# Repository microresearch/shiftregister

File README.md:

# shiftregister
Software and hardware for the Shift Register project:

http://shiftregister.info/

NOW moved to: https://github.com/shiftregister/shiftregister

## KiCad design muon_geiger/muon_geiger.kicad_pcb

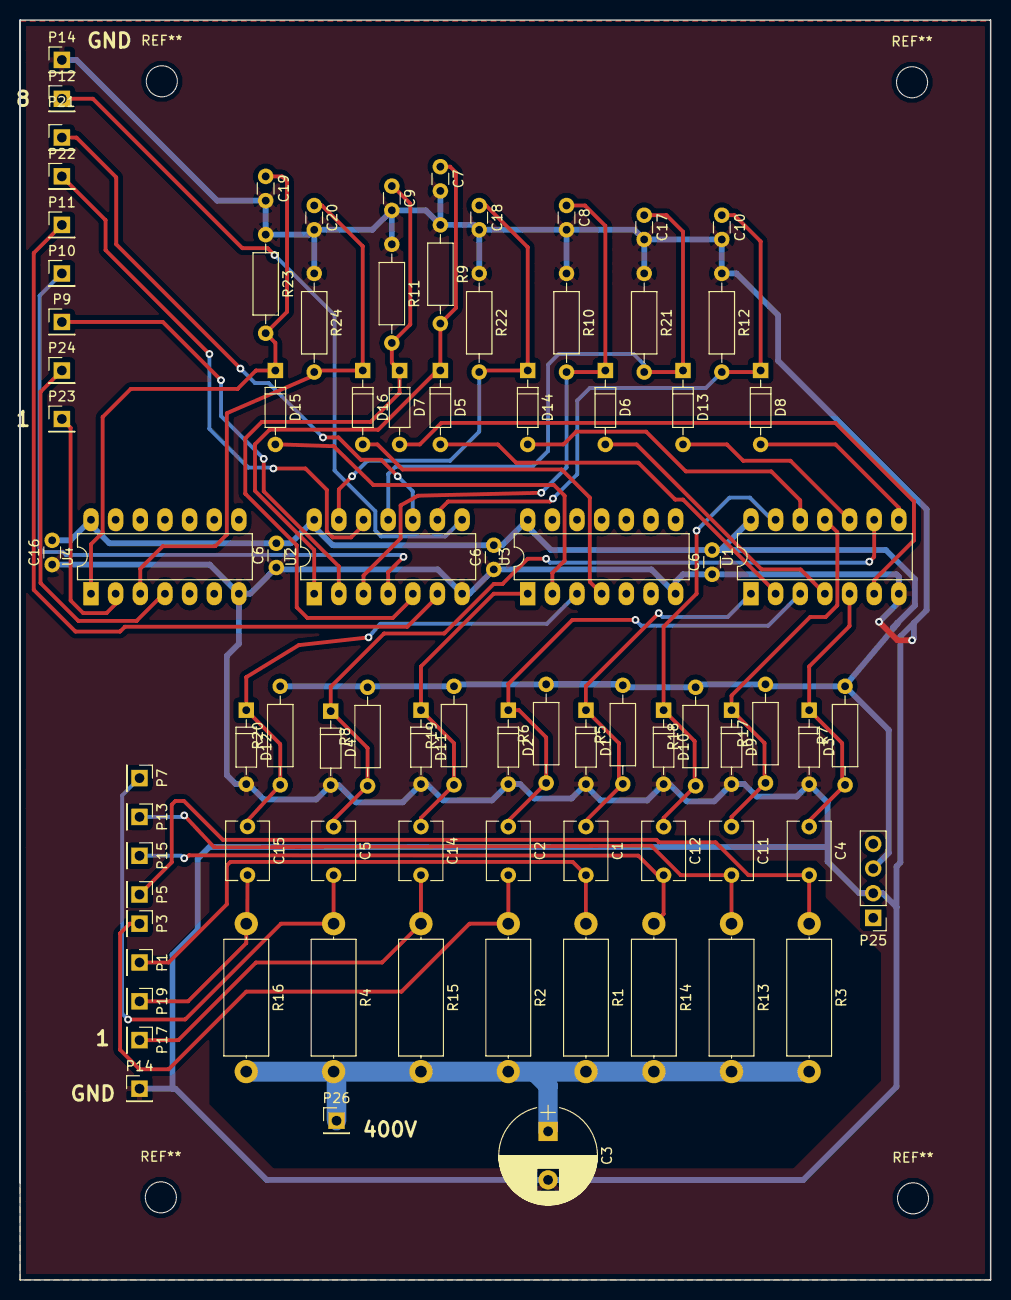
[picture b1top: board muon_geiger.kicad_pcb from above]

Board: 2 copper layers, 100.0 x 129.8 mm, 85 parts (0 on the bottom side), 43 nets.

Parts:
C1, C2, C4, C5, C11, C12, C14, C15: 10p; C_Disc_D6.0mm_W4.4mm_P5.00mm
C3: 1uF; CP_Radial_D10.0mm_P5.00mm
C6, C6#2, C6#3, C16: 100N; C_Disc_D3.0mm_W1.6mm_P2.50mm
C7, C8, C9, C10, C17, C18, C19, C20: 4n7; C_Disc_D3.0mm_W1.6mm_P2.50mm
D1, D2, D3, D4, D9, D10, D11, D12: 5V3; D_DO-35_SOD27_P7.62mm_Horizontal
D5, D6, D7, D8, D13, D14, D15, D16: 1N914; D_DO-35_SOD27_P7.62mm_Horizontal
P1, P3, P5, P7, P9, P10, P11, P12, P13, P14, P14#2, P15, P17, P19, P21, P22, P23, P24, P26: CONN_01X01; Pin_Header_Straight_1x01_Pitch2.54mm
P25: CONN_01X04; Pin_Header_Straight_1x04_Pitch2.54mm
R1, R2, R3, R4, R13, R14, R15, R16: 10M; R_Axial_DIN0414_L11.9mm_D4.5mm_P15.24mm_Horizontal
R5, R6, R7, R8, R17, R18, R19, R20: 100K; R_Axial_DIN0207_L6.3mm_D2.5mm_P10.16mm_Horizontal
R9, R10, R11, R12, R21, R22, R23, R24: 220K; R_Axial_DIN0207_L6.3mm_D2.5mm_P10.16mm_Horizontal
U1, U3: 74HC14; DIP-14_W7.62mm_LongPads
U2, U4: 74LS14; DIP-14_W7.62mm_LongPads

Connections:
+5V: C6.2, C6#2.2, C6#3.2, C16.2, P25.3, R5.2, R6.2, R7.2, R8.2, R17.2, R18.2, R19.2, R20.2, U1.14, U2.14, U3.14, U4.14
/400V: C3.1, P26.1, R1.2, R2.2, R3.2, R4.2, R13.2, R14.2, R15.2, R16.2
GND: C3.2, C6.1, C6#2.1, C6#3.1, C7.2, C8.2, C9.2, C10.2, C16.1, C17.2, C18.2, C19.2, C20.2, D1.2, D2.2, D3.2, D4.2, D9.2, D10.2, D11.2, D12.2, P14.1, P14#2.1, P25.2, R9.1, R10.1, R11.1, R12.1, R21.1, R22.1, R23.1, R24.1, U1.7, U2.7, U3.7, U4.7
unnamed: C1.1, D1.1, R5.1, U1.1
unnamed: C1.2, P1.1, R1.1
unnamed: C2.1, D2.1, R6.1, U1.3
unnamed: C2.2, P3.1, R2.1
unnamed: C4.1, D3.1, R7.1, U1.5
unnamed: C4.2, P5.1, R3.1
unnamed: C5.1, D4.1, R8.1, U1.9
unnamed: C5.2, P7.1, R4.1
unnamed: C7.1, D5.1, R9.2, U2.1
unnamed: C8.1, D6.1, R10.2, U2.3
unnamed: C9.1, D7.1, R11.2, U2.5
unnamed: C10.1, D8.1, R12.2, U2.9
unnamed: C11.1, D9.1, R17.1, U1.11
unnamed: C11.2, P13.1, R13.1
unnamed: C12.1, D10.1, R18.1, U1.13
unnamed: C12.2, P15.1, R14.1
unnamed: C14.1, D11.1, R19.1, U3.1
unnamed: C14.2, P17.1, R15.1
unnamed: C15.1, D12.1, R20.1, U3.3
unnamed: C15.2, P19.1, R16.1
unnamed: C17.1, D13.1, R21.2, U2.11
unnamed: C18.1, D14.1, R22.2, U2.13
unnamed: C19.1, D15.1, R23.2, U4.1
unnamed: C20.1, D16.1, R24.2, U4.3
unnamed: D5.2, U1.2
unnamed: D6.2, U1.4
unnamed: D7.2, U1.6
unnamed: D8.2, U1.8
unnamed: D13.2, U1.10
unnamed: D14.2, U1.12
unnamed: D15.2, U3.2
unnamed: D16.2, U3.4
unnamed: P9.1, U2.2
unnamed: P10.1, U2.4
unnamed: P11.1, U2.6
unnamed: P12.1, U2.8
unnamed: P21.1, U2.10
unnamed: P22.1, U2.12
unnamed: P23.1, U4.2
unnamed: P24.1, U4.4

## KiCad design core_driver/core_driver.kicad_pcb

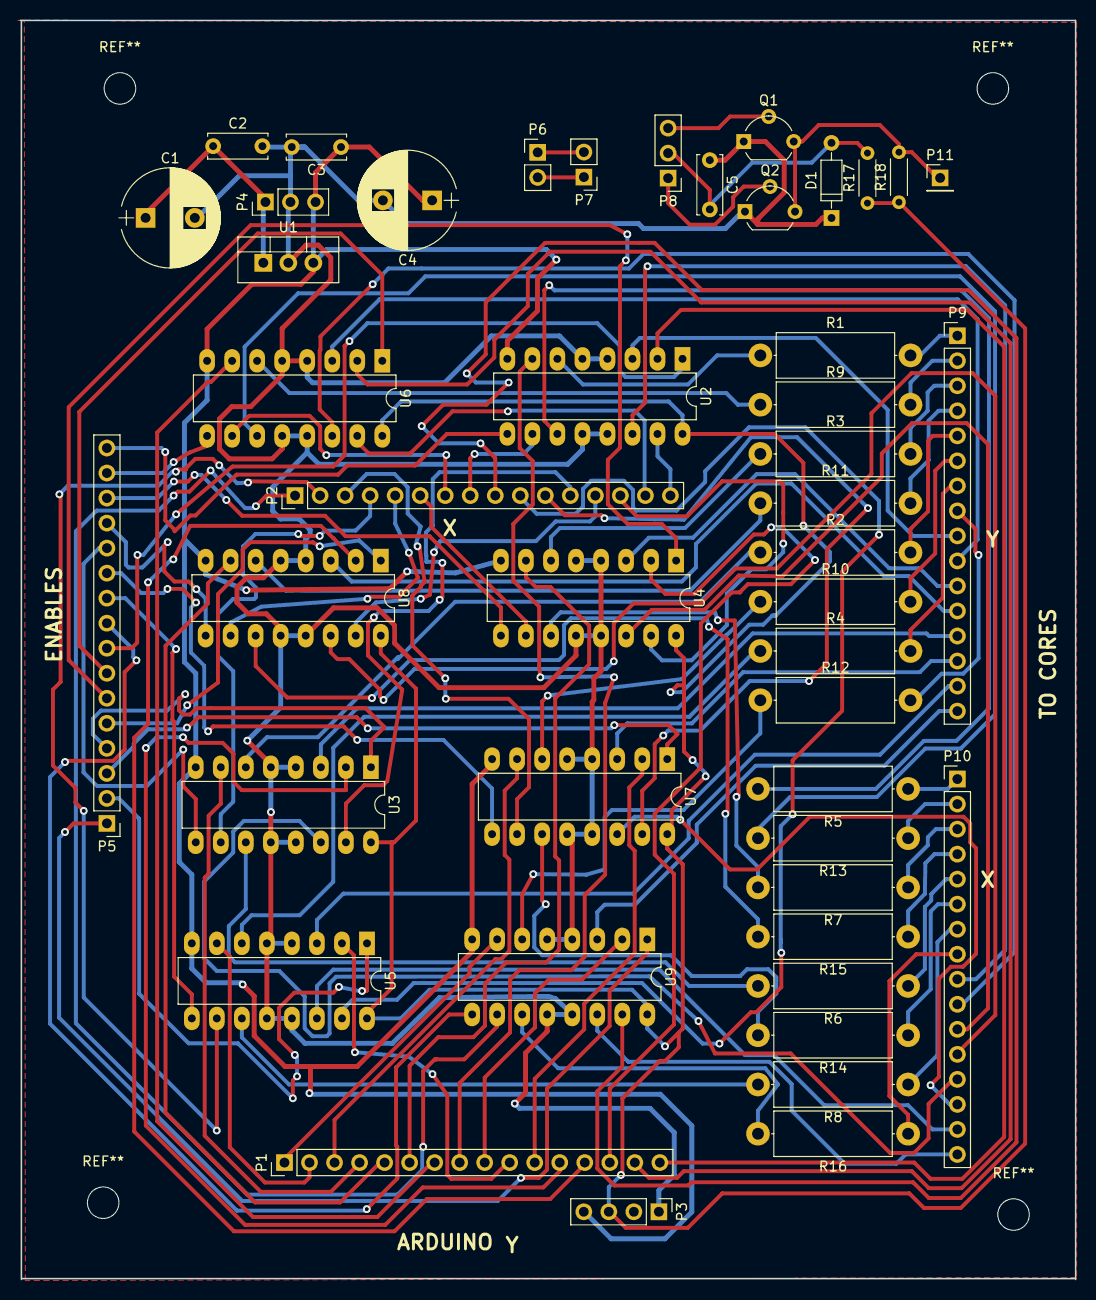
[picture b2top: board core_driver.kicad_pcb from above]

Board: 2 copper layers, 107.1 x 127.8 mm, 46 parts (0 on the bottom side), 106 nets.

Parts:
C1, C4: 10U; CP_Radial_D10.0mm_P5.00mm
C2, C3, C5: 100N; C_Disc_D6.0mm_W2.5mm_P5.00mm
D1: 1N4148; D_DO-35_SOD27_P7.62mm_Horizontal
P1, P2, P5, P9, P10: CONN_01X16; Pin_Header_Straight_1x16_Pitch2.54mm
P3: CONN_01X04; Pin_Header_Straight_1x04_Pitch2.54mm
P4, P8: CONN_01X03; Pin_Header_Straight_1x03_Pitch2.54mm
P6, P7: CONN_01X02; Pin_Header_Straight_1x02_Pitch2.54mm
P11: SENSE_DATA; Pin_Header_Straight_1x01_Pitch2.54mm
Q1, Q2: 2n3904; TO-92_Molded_Wide
R1, R2, R3, R4, R5, R6, R7, R8, R9, R10, R11, R12, R13, R14, R15, R16: 10R; R_Axial_DIN0414_L11.9mm_D4.5mm_P15.24mm_Horizontal
R17, R18: 10K; R_Axial_DIN0204_L3.6mm_D1.6mm_P5.08mm_Horizontal
U1: 7805; TO-220_Vertical
U2, U3, U4, U5, U6, U7, U8, U9: SN754410; DIP-16_W7.62mm_LongPads

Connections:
+5V: C3.1, C4.1, P3.4, P4.3, U1.3, U2.8, U3.8, U4.8, U5.8, U6.8, U7.8, U8.8, U9.8
/+9V: C1.1, C2.1, P4.1, U1.1
/EN_X0: P5.16, U2.9
/EN_X1: P5.15, U6.9
/EN_X2: P5.14, U4.9
/EN_X3: P5.13, U8.9
/EN_X4: P5.12, U3.9
/EN_X5: P5.11, U7.9
/EN_X6: P5.10, U5.9
/EN_X7: P5.9, U9.9
/EN_Y0: P5.8, U2.1
/EN_Y1: P5.7, U6.1
/EN_Y2: P5.6, U4.1
/EN_Y3: P5.5, U8.1
/EN_Y4: P5.4, U3.1
/EN_Y5: P5.3, U7.1
/EN_Y6: P5.2, U5.1
/EN_Y7: P5.1, U9.1
/HI_X0: P2.8, U2.10
/HI_X1: P2.7, U6.10
/HI_X2: P2.6, U4.10
/HI_X3: P2.5, U8.10
/HI_X4: P2.4, U3.10
/HI_X5: P2.3, U7.10
/HI_X6: P2.2, U5.10
/HI_X7: P2.1, U9.10
/HI_Y0: P1.8, U2.7
/HI_Y1: P1.7, U6.7
/HI_Y2: P1.6, U4.7
/HI_Y3: P1.5, U8.7
/HI_Y4: P1.4, U3.7
/HI_Y5: P1.3, U7.7
/HI_Y6: P1.2, U5.7
/HI_Y7: P1.1, U9.7
/IN_X0: P10.1, R5.1
/IN_X1: P10.2, R13.1
/IN_X2: P10.3, R7.1
/IN_X3: P10.4, R15.1
/IN_X4: P10.5, R6.1
/IN_X5: P10.6, R14.1
/IN_X6: P10.7, R8.1
/IN_X7: P10.8, R16.1
/IN_Y0: P9.1, R1.2
/IN_Y1: P9.2, R9.2
/IN_Y2: P9.3, R3.2
/IN_Y3: P9.4, R11.2
/IN_Y4: P9.5, R2.2
/IN_Y5: P9.6, R10.2
/IN_Y6: P9.7, R4.2
/IN_Y7: P9.8, R12.2
/LOGIC_PWR: P3.3, R17.1, R18.1, U2.16, U3.16, U4.16, U5.16, U6.16, U7.16, U8.16, U9.16
/LOW_X0: P2.16, U2.15
/LOW_X1: P2.15, U6.15
/LOW_X2: P2.14, U4.15
/LOW_X3: P2.13, U8.15
/LOW_X4: P2.12, U3.15
/LOW_X5: P2.11, U7.15
/LOW_X6: P2.10, U5.15
/LOW_X7: P2.9, U9.15
/LOW_Y0: P1.16, U2.2
/LOW_Y1: P1.15, U6.2
/LOW_Y2: P1.14, U4.2
/LOW_Y3: P1.13, U8.2
/LOW_Y4: P1.12, U3.2
/LOW_Y5: P1.11, U7.2
/LOW_Y6: P1.10, U5.2
/LOW_Y7: P1.9, U9.2
/OUT_X0: P10.9, U2.14
/OUT_X1: P10.10, U6.14
/OUT_X2: P10.11, U4.14
/OUT_X3: P10.12, U8.14
/OUT_X4: P10.13, U3.14
/OUT_X5: P10.14, U7.14
/OUT_X6: P10.15, U5.14
/OUT_X7: P10.16, U9.14
/OUT_Y0: P9.9, U2.3
/OUT_Y1: P9.10, U6.3
/OUT_Y2: P9.11, U4.3
/OUT_Y3: P9.12, U8.3
/OUT_Y4: P9.13, U3.3
/OUT_Y5: P9.14, U7.3
/OUT_Y6: P9.15, U5.3
/OUT_Y7: P9.16, U9.3
GND: C1.2, C2.2, C3.2, C4.2, C5.1, D1.1, P3.1, P4.2, Q1.1, Q2.1, U1.2, U2.4, U2.5, U2.12, U2.13, U3.4, U3.5, U3.12, U3.13, U4.4, U4.5, U4.12, U4.13, U5.4, U5.5, U5.12, U5.13, U6.4, U6.5, U6.12, U6.13, U7.4, U7.5, U7.12, U7.13, U8.4, U8.5, U8.12, U8.13, U9.4, U9.5, U9.12, U9.13
unnamed: C5.2, D1.2, P8.2, R17.2
unnamed: P6.1, P7.2
unnamed: P6.2, P7.1
unnamed: P8.1, Q2.2
unnamed: P8.3, Q1.2
unnamed: P11.1, Q1.3, Q2.3, R18.2
unnamed: R1.1, U2.6
unnamed: R2.1, U3.6
unnamed: R3.1, U4.6
unnamed: R4.1, U5.6
unnamed: R5.2, U2.11
unnamed: R6.2, U3.11
unnamed: R7.2, U4.11
unnamed: R8.2, U5.11
unnamed: R9.1, U6.6
unnamed: R10.1, U7.6
unnamed: R11.1, U8.6
unnamed: R12.1, U9.6
unnamed: R13.2, U6.11
unnamed: R14.2, U7.11
unnamed: R15.2, U8.11
unnamed: R16.2, U9.11

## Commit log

2017-03-07 first for mapping softwares
2017-06-29 added muon and entropy processing/plotting
2017-07-13 hardware
2017-07-19 added dirs
2017-07-19 added dir/dels
2017-07-25 NOW moved to: https://github.com/shiftregister/shiftregister
